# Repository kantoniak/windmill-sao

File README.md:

# Windmill SAO

> [!IMPORTANT]
> ### **Hackaday Europe 2026** and **Open Hardware Summit 2026** folks:
> Please use `README.md` from the [`rev1-rc2-wip` branch](https://github.com/kantoniak/windmill-sao/tree/kantoniak/rev1-rc2-wip).

Dutch [tower mill](https://en.wikipedia.org/wiki/Tower_mill) in a [SAO (Simple Add-on/Shitty Add-on)](https://hackaday.io/project/52950-shitty-add-ons/log/159806-introducing-the-shitty-add-on-v169bis-standard) form factor.

The project consists of:
* 3D printed enclosure (see [enclosure/](./enclosure/))
* PCB design (see [hardware/](./hardware/))
* PCB firmware (see [firmware/](./firmware/))

Some components are available in the repository only as scripts that generate resources. See the releases for generated outputs.

## Enclosure

Enclosure is built from a headless Python script that generates a FreeCAD model. Use FreeCAD 1.0 stable.

### Windows

1. Add FreeCAD's `bin/` directory to `PATH`. Usually `C:\Program Files\FreeCAD 1.0\bin\`
2. Generate the model:

    ```powershell
    cd enclosure/
    freecadcmd model.py
    ```

### Linux

1. Install FreeCAD:

    ```bash
    # Install FreeCAD
    sudo add-apt-repository ppa:freecad-maintainers/freecad-stable
    sudo apt update
    sudo apt install freecad
    ```
2. Generate the model:

    ```powershell
    cd enclosure/
    freecadcmd model.py
    ```

## PCB

The PCB was designed in KiCad. See `hardware/` for the source files and releases for generated outputs.

<p align="center">
  
</p>

## Firmware

The PCB is built around CH32V003 and the firmware uses open-source [ch32fun](https://github.com/cnlohr/ch32fun) stack. Use PlatformIO to program the chip.

## License

[Open source hardware project: `[OSHW] PL000026`<br />

](https://certification.oshwa.org/pl000026.html)

This project in its entirety is licensed under the `CERN-OHL-S-2.0` license - see the [LICENSE](LICENSE) file for details.

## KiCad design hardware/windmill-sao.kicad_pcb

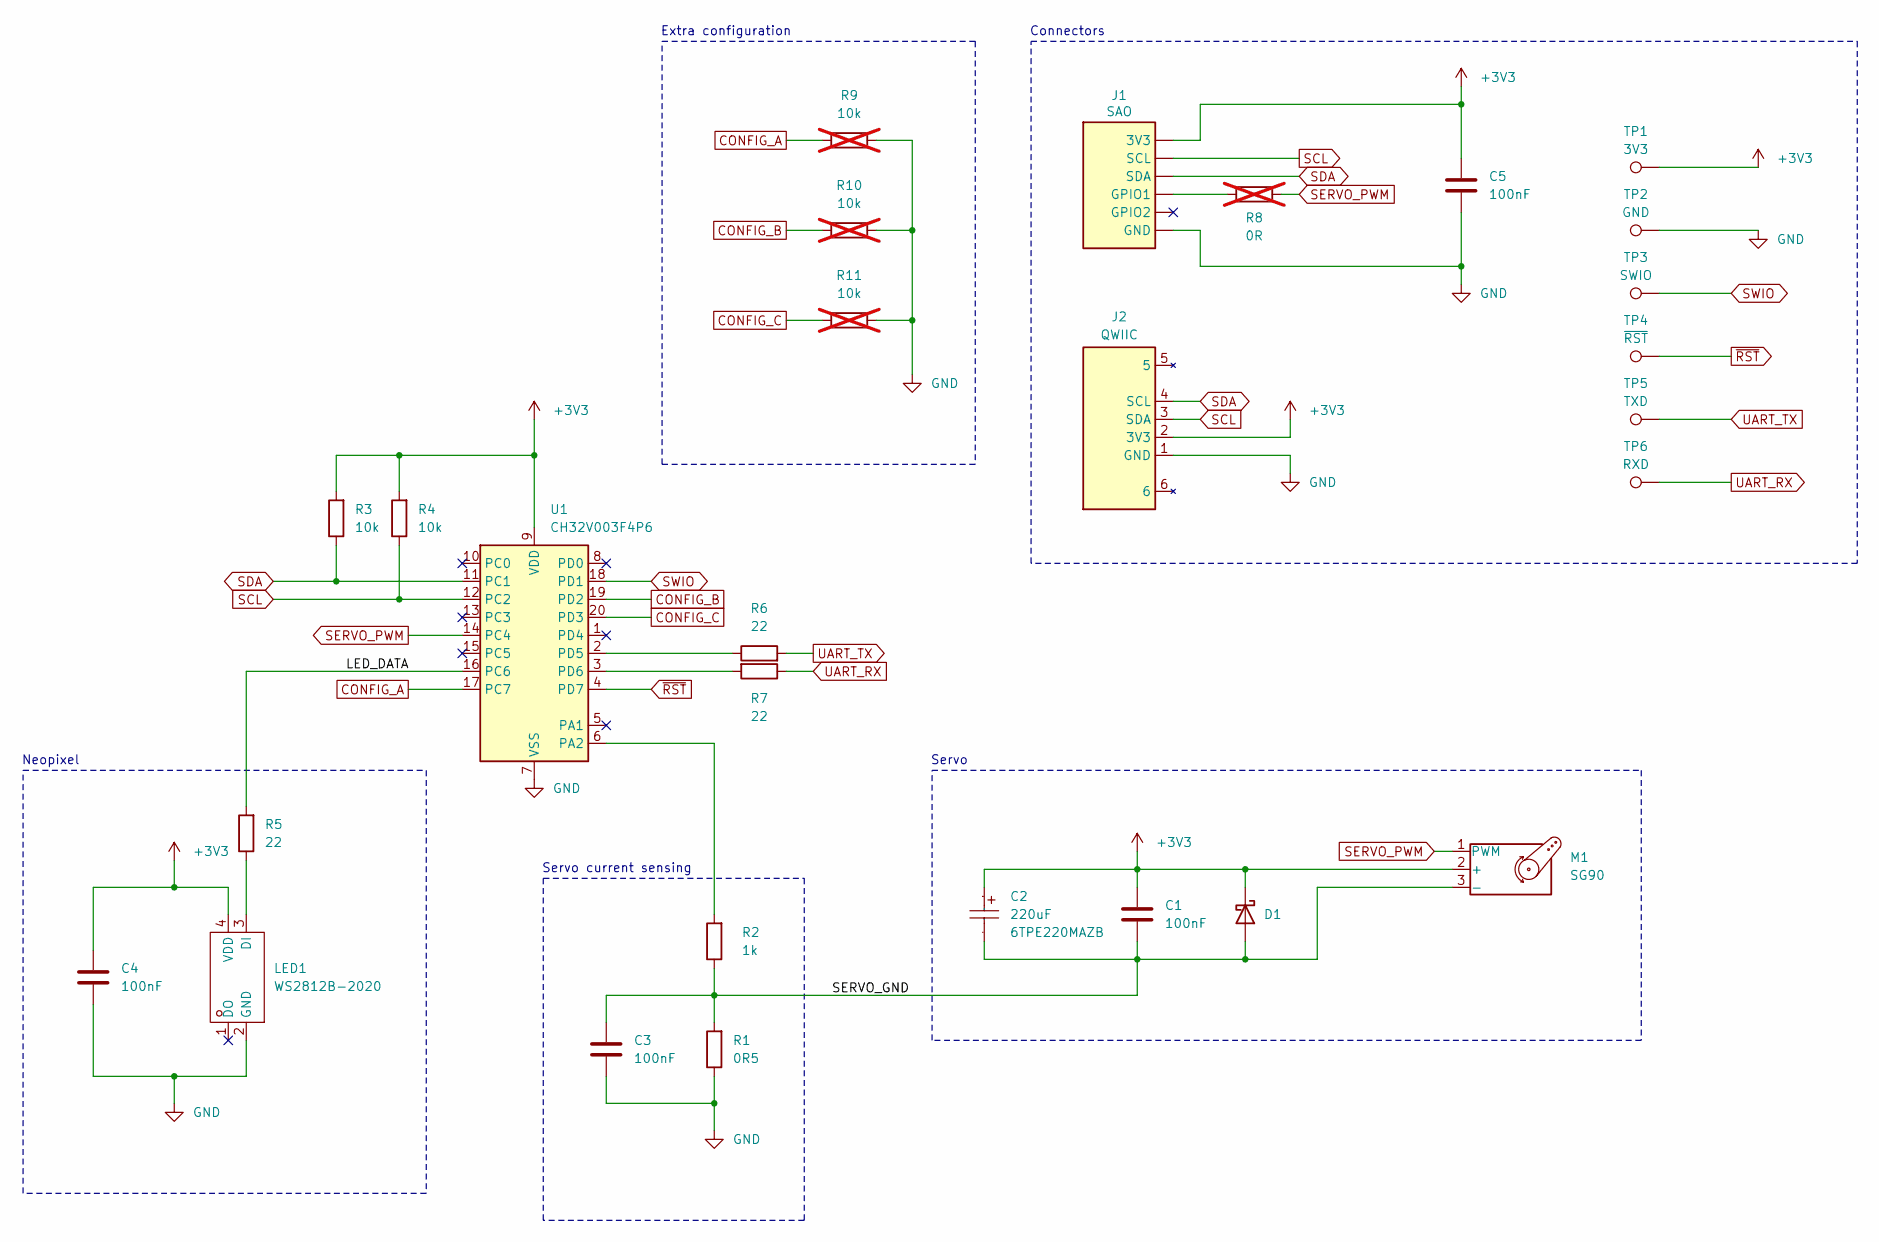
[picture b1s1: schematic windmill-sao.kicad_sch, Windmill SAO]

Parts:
C1, C3, C4, C5: 100nF; C_0603_1608Metric_Pad1.08x0.95mm_HandSolder; LCSC Part # C14663
C2: 220uF; CP_EIA-3528-21_Kemet-B_HandSolder; Manufacturer Part 6TPE220MAZB; LCSC Part Name 220uF ±20% 6.3V MSL=3拆包后请尽快使用
D1: D_Schottky; D_SMA; LCSC Part # C2480
J1: SAO; SAO_Header_Addon_Side
J2: QWIIC; JST_SH_SM04B-SRSS-TB_1x04-1MP_P1.00mm_Horizontal; Manufacturer Part SM04B-SRSS-TB(LF)(SN); LCSC Part # C160404
LED1: LED-SMD_4P-L2.0-W2.0-TL_WS2812B-2020; Manufacturer Part WS2812B-2020; JLCPCB Part # C965555
M1: SG90; PinHeader_1x03_P2.54mm_Vertical_SG90
R1: 0R5; R_1206_3216Metric_Pad1.30x1.75mm_HandSolder; LCSC Part # C25340
R2: 1k; R_0603_1608Metric_Pad0.98x0.95mm_HandSolder; LCSC Part # C21190
R3, R4: 10k; R_0603_1608Metric_Pad0.98x0.95mm_HandSolder; LCSC Part # C25804
R5, R6, R7: 22; R_0603_1608Metric_Pad0.98x0.95mm_HandSolder; LCSC Part # C23345
R8: 0R; R_0603_1608Metric_Pad0.98x0.95mm_HandSolder; not fitted
R9, R10, R11: 10k; R_0603_1608Metric_Pad0.98x0.95mm_HandSolder; not fitted
TP1: 3V3; TestPoint_Pad_D1.5mm
TP2: GND; TestPoint_Pad_D1.5mm
TP3: SWIO; TestPoint_Pad_D1.5mm
TP4: ~{RST}; TestPoint_Pad_D1.5mm
TP5: TXD; TestPoint_Pad_D1.5mm
TP6: RXD; TestPoint_Pad_D1.5mm
U1: CH32V003F4P6; TSSOP-20_4.4x6.5mm_P0.65mm; LCSC Part # C5187096

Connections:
+3V3: C1.1, C2.1, C4.1, C5.1, D1.1 (K), J1.6 (3V3), J2.2 (3V3), LED1.4 (VDD), M1.2 (+), R3.2, R4.2, TP1.1 (1_1), U1.9 (VDD)
/LED_DATA: R5.2, U1.16 (PC6)
/SERVO_GND: C1.2, C2.2, C3.1, D1.2 (A), M1.3 (-), R1.2, R2.1
CONFIG_A: R9.1, U1.17 (PC7)
CONFIG_B: R10.2, U1.19 (PD2)
CONFIG_C: R11.2, U1.20 (PD3)
GND: C3.2, C4.2, C5.2, J1.1 (GND), J2.1 (GND), LED1.2 (GND), R1.1, R9.2, R10.1, R11.1, TP2.1 (1_1), U1.7 (VSS)
unnamed: J1.4 (GPIO1), R8.1
unnamed: LED1.3 (DI), R5.1
unnamed: R2.2, U1.6 (PA2)
unnamed: R6.1, U1.2 (PD5)
unnamed: R7.2, U1.3 (PD6)
SCL: J1.2 (SCL), J2.3 (SDA), R4.1, U1.12 (PC2)
SDA: J1.5 (SDA), J2.4 (SCL), R3.1, U1.11 (PC1)
SERVO_PWM: M1.1 (PWM), R8.2, U1.14 (PC4)
SWIO: TP3.1 (1_1), U1.18 (PD1)
UART_RX: R7.1, TP6.1 (1_1)
UART_TX: R6.2, TP5.1 (1_1)
~RST: TP4.1 (1_1), U1.4 (PD7)

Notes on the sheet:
Extra configuration
Servo current sensing
Connectors
Neopixel
Servo

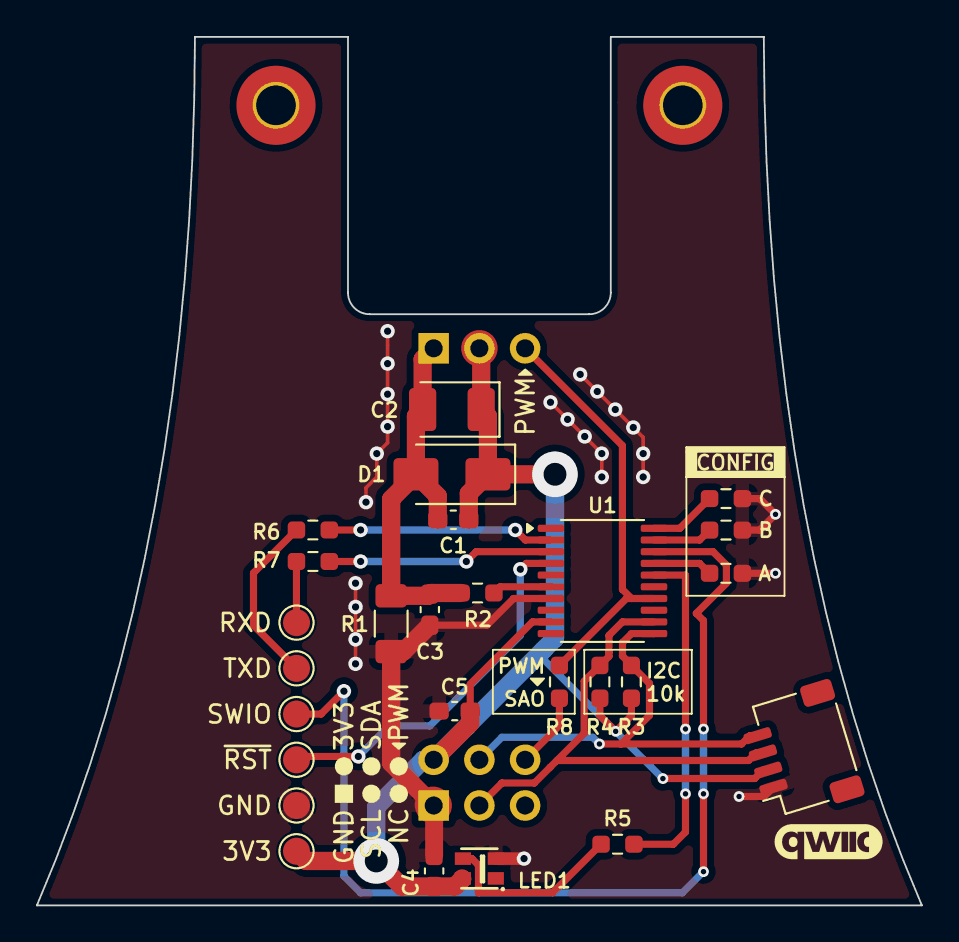
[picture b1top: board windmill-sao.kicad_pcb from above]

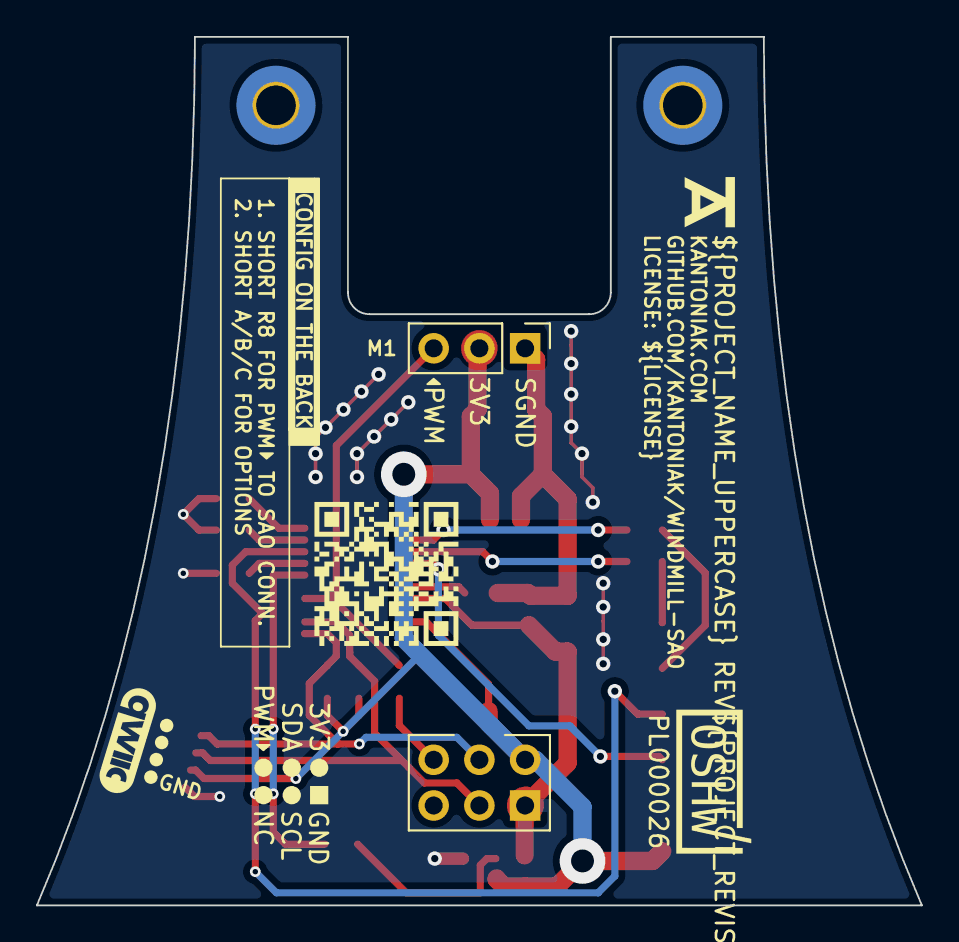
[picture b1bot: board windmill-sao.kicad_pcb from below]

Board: 2 copper layers, 49.2 x 48.2 mm, 32 parts (3 on the bottom side), 19 nets.

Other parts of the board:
MountingHole1, MountingHole2: MountingHole_2.2mm_M2_Pad_TopBottom
QWIIC_Back: QWIIC_Back; qwiic_logo
QWIIC_Front: QWIIC_Front; qwiic_logo

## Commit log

2025-12-27 Hello, windmill-sao!
2025-12-27 Create minimal FreeCAD script
2025-12-27 Add VS Code settings
2025-12-27 Add Linux build instructions
2025-12-27 Convert FreeCAD model to parameter-driven sketch
2025-12-27 Refactor param and constraint creation
2025-12-27 Swap cube for SG90 (WIP, base and flange)
2025-12-29 Add bushing to the SG90 model
2025-12-29 Add teeth to the SG90 model
2025-12-29 Add note on PartDesign::Line deprecation
2025-12-29 Fix flange sketch geometry issues
2025-12-29 Move SG90 creation to a function, tidy up recomputes
2025-12-29 Make readability and performance improvements
2025-12-31 Fix servo position around origin
2025-12-31 Add supporting datum geometry
2025-12-31 Add tower's side-view spline
2025-12-31 Add tower's angle-view spline
2026-01-01 Create cloned splines
2026-01-01 Clean up sketch clones
2026-01-01 Build vertical surfaces
2026-01-01 Replace deprecated `Draft.clone` with `Draft.make_clone`
2026-01-03 Create top and bottom faces of tower base
2026-01-03 Fix placement of side splines
2026-01-03 Create a solid from the tower splines
2026-01-03 Add tower base
2026-01-03 Refactor code and regroup objects
2026-01-04 Define Tower_Top_Back
2026-01-10 Update stale comments
2026-01-10 Build back view sketch
2026-01-10 Cut tower's back side
2026-01-10 Build PCB object
2026-01-10 Move enclosure-specific ignores to enclosure/
2026-01-10 Export PCB outline as DXF from FreeCAD script
2026-01-10 Set up Kicad project
2026-01-18 Fix gitignore path for FreeCAD exports
2026-01-18 Update SG90 measurements
2026-01-18 Fix global geometry positioning expressions
2026-01-18 Add cap base
2026-01-18 Create servo tunnel
2026-01-18 Add STL export
2026-01-18 Add temporary cap for tunnel size testing
2026-01-18 Move cap loft to vertical center between base and bearing
2026-01-19 Add cap floor
2026-01-19 Minor improvements
    * Replace `Part::MultiFuse` with `Part::Compound` where possible
    * Set default values for some `Part.Circle`s to avoid console errors
2026-01-20 Encapsulate floor `PartDesign::Body` in a subobject
2026-01-20 Build supporting geometry for the roof
2026-02-18 Clean up Cap supporting geometry, extract floor sketch, divide side edge at roof ridge points
2026-02-19 Add roof side ribs
2026-02-20 Fix continuous loop helper
2026-02-20 Add front roof sketches
2026-02-20 Add roof ridge sketch and first side surface
2026-02-21 Extend roof side surface to rear gable
2026-02-21 Add flat surfaces and create roof solid
2026-02-21 Clean up Cap compound creation
2026-02-21 Remove temporary cap shape
2026-02-22 Build cap front assembly with shingles
2026-03-09 Set up firmware project (`ch32fun` on `genericCH32V003F4P6`)
2026-03-09 Convert blink sketch to fade in/out using PWM timer
2026-04-09 Slice away back of the cap
2026-04-09 Cut away a support shape for 3D printing
2026-04-11 Add mounting holes to PCB outline
2026-04-11 Update DXF export to include all coplanar faces
2026-04-11 Add heat insert holes in the tower
2026-04-11 Import board outline into Edge.Cuts and add M2 pads
2026-04-11 Import STEP file with PCB
2026-04-12 Add EXPORT_STL option
2026-04-13 Add space-sensitive components to the PCB
2026-04-13 Add main PCB components
2026-04-13 Ignore files from fabrication-toolkit-options
2026-04-21 Add passives to the schematic, PCB WIP
2026-04-26 Add configuration resistors, route the PCB
2026-04-26 Add QWIIC logo and supplier part numbers
2026-04-26 Clean up PCB
    * Add GND fill on front layer and via stitching
    * Use smaller text size for designators
    * Place info silkscreen and QR code
    * Add 3D model for SAO connector
2026-04-27 Add C5 and clean up silkscreen even more
2026-04-27 Add LICENSE and project metadata
2026-04-27 Fix thermal release violations
2026-05-01 Add OSHWA cert no. to silkscreen
2026-05-01 Add OSHWA cert no. to README
2026-05-11 Update PCB preview
2026-05-12 Update enclosure previews
2026-05-12 Enclosure: extract STL extraction function
2026-05-13 WIP (firmware/)
2026-05-13 WIP (enclosure/)
2026-05-13 WIP (firmware spec)
2026-05-14 WIP2 (firmmware/)
2026-05-14 Add assembly instructions
2026-05-14 Add a note to Hackaday Europe 2026 users
2026-05-16 Update assembly instructions
2026-05-23 Update Hackaday Europe 2026 notice in README

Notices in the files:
parts and their libraries:
LICENSE: CERN-OHL-S-2.0
